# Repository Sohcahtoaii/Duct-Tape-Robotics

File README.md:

Robot pour la RoboCup – Catégorie Rescue Line Junior

Les fichiers de conception mécanique (CAO) ainsi que ceux de la carte électronique sont disponibles dans ce dépôt.

Une liste complète des pièces utilisées, avec des liens vers les composants, est également fournie.
Cependant, il est fortement recommandé de vérifier les empreintes (footprints) et les dimensions avant tout achat, afin d’éviter les erreurs de compatibilité.

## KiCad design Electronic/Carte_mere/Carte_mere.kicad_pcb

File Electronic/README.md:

Carte électronique du robot, liste des composants et librairy avec les componsants utilisés

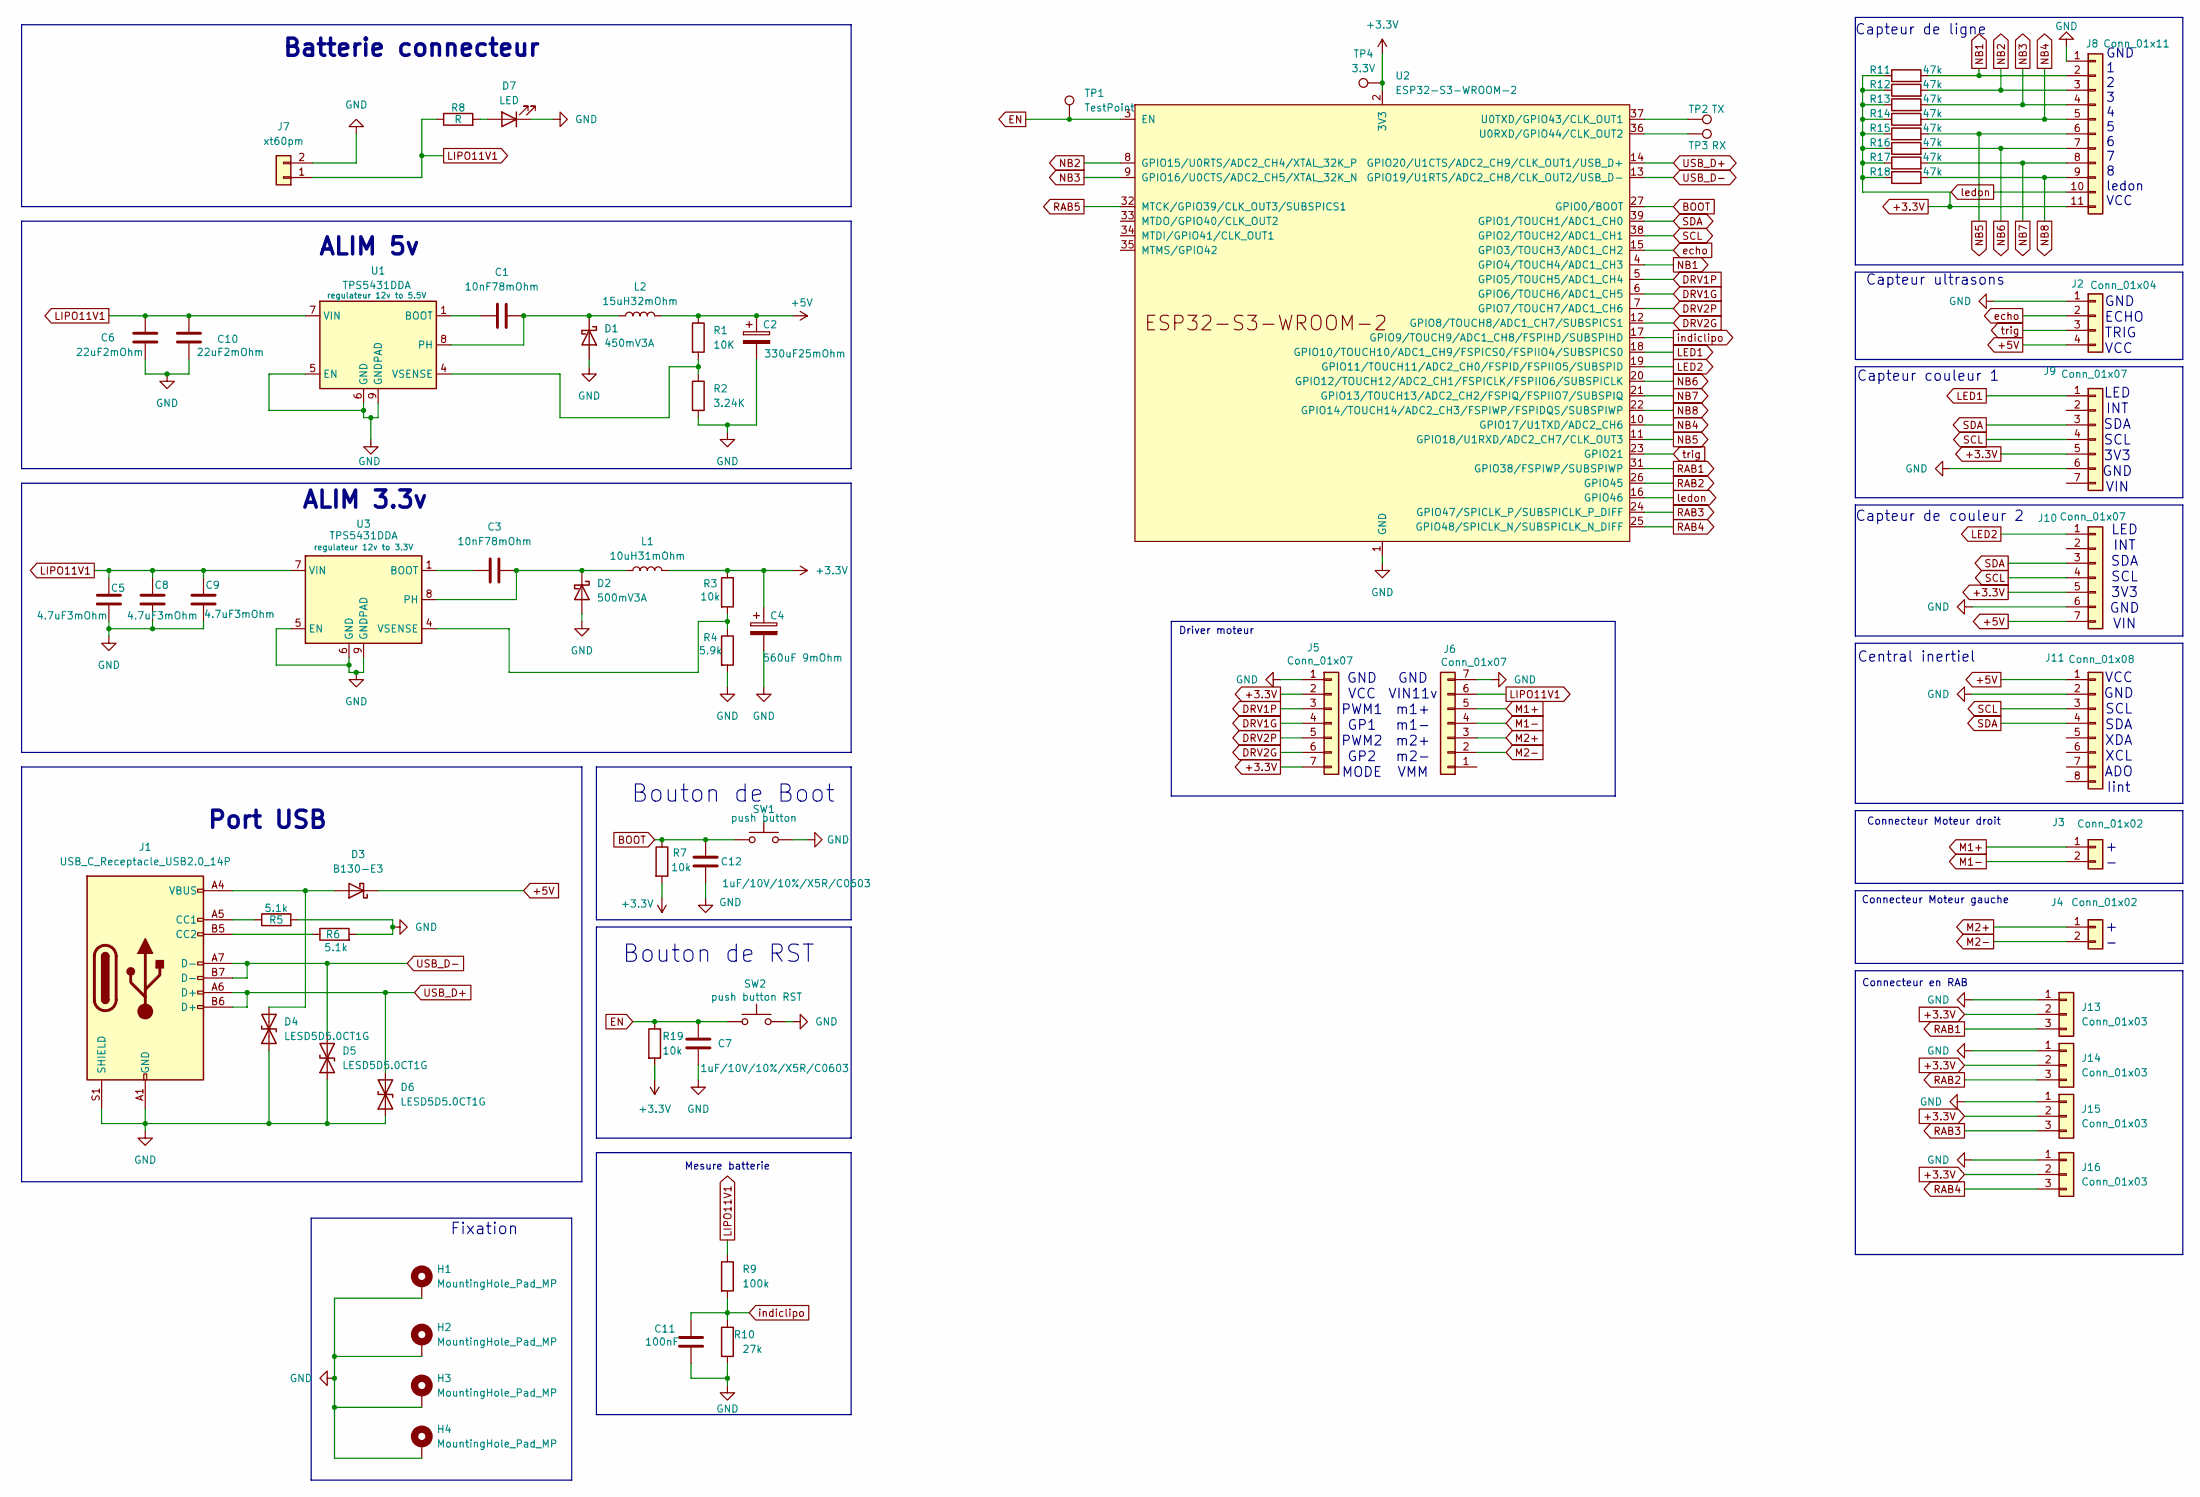
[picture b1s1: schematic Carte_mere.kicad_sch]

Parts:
C1, C3: 10nF78mOhm; C_0805_2012Metric_Pad1.18x1.45mm_HandSolder
C2: 330uF25mOhm; CP_Elec_10x12.6
C4: 560uF 9mOhm; CP_Elec_8x10.5
C5, C8, C9: 4.7uF3mOhm; C_0805_2012Metric_Pad1.18x1.45mm_HandSolder
C6, C10: 22uF2mOhm; C_0805_2012Metric_Pad1.18x1.45mm_HandSolder
C7, C12: 1uF/10V/10%/X5R/C0603; C_0805_2012Metric_Pad1.18x1.45mm_HandSolder
C11: 100nF; C_0805_2012Metric_Pad1.18x1.45mm_HandSolder
D1: 450mV3A; B340LA
D2: 500mV3A; B340LA
D3: B130-E3; D_SMA
D4, D5, D6: LESD5D5.0CT1G; LESD5D50CT1G
D7: LED; LED_0805_2012Metric_Pad1.15x1.40mm_HandSolder
H1, H2, H3, H4: MountingHole_Pad_MP; MountingHole_3.2mm_M3_DIN965_Pad_TopBottom
J1: USB_C_Receptacle_USB2.0_14P; USB_C_Receptacle_GCT_USB4105-xx-A_16P_TopMnt_Horizontal
J2: Conn_01x04; Molex_PicoBlade_53398-0471_1x04-1MP_P1.25mm_Vertical
J3, J4: Conn_01x02; 2843922
J5: Conn_01x07; PinSocket_1x07_P2.54mm_Vertical_SMD_Pin1Right
J6: Conn_01x07; PinSocket_1x07_P2.54mm_Vertical_SMD_Pin1Left
J7: xt60pm; XT60PWM
J8: Conn_01x11; Molex_PicoBlade_53261-1171_1x11-1MP_P1.25mm_Horizontal
J9, J10: Conn_01x07; Molex_PicoBlade_53261-0771_1x07-1MP_P1.25mm_Horizontal
J11: Conn_01x08; PinSocket_1x08_P2.54mm_Vertical_SMD_Pin1Right
J13, J14, J15, J16: Conn_01x03; PinHeader_1x03_P2.54mm_Vertical
L1: 10uH31mOhm; INDPM102100X510N
L2: 15uH32mOhm; INDPM120120X620N
R1: 10K; R_0805_2012Metric_Pad1.20x1.40mm_HandSolder
R2: 3.24K; R_0805_2012Metric_Pad1.20x1.40mm_HandSolder
R3, R7, R19: 10k; R_0805_2012Metric_Pad1.20x1.40mm_HandSolder
R4: 5.9k; R_0805_2012Metric_Pad1.20x1.40mm_HandSolder
R5, R6: 5.1k; R_0805_2012Metric_Pad1.20x1.40mm_HandSolder
R8: R; R_0805_2012Metric_Pad1.20x1.40mm_HandSolder
R9: 100k; R_0805_2012Metric_Pad1.20x1.40mm_HandSolder
R10: 27k; R_0805_2012Metric_Pad1.20x1.40mm_HandSolder
R11, R12, R13, R14, R15, R16, R17, R18: 47k; R_0805_2012Metric_Pad1.20x1.40mm_HandSolder
SW1: push button; SW_PUSH_6mm_H5mm
SW2: push button RST; SW_PUSH_6mm_H5mm
TP1: TestPoint; TestPoint_Pad_D1.5mm
TP2: TX; TestPoint_Pad_D1.5mm
TP3: RX; TestPoint_Pad_D1.5mm
TP4: 3.3V; TestPoint_Pad_D1.5mm
U1, U3: TPS5431DDA; TI_SO-PowerPAD-8_ThermalVias
U2: ESP32-S3-WROOM-2

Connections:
+3.3V: C4.1, J5.2, J5.7, J8.11, J9.5, J10.5, J13.2, J14.2, J15.2, J16.2, L1.2, R3.1, R7.2, R11.1, R12.1, R13.1, R14.1, R15.1, R16.1, R17.1, R18.1, R19.2, TP4.1, U2.2 (3V3)
+5V: C2.1, D3.1 (K), J2.4, J10.7, J11.1, L2.2, R1.1
BOOT: C12.1, R7.1, SW1.1, U2.27 (GPIO0/BOOT)
DRV1G: J5.4, U2.6 (GPIO6/TOUCH6/ADC1_CH5)
DRV1P: J5.3, U2.5 (GPIO5/TOUCH5/ADC1_CH4)
DRV2G: J5.6, U2.12 (GPIO8/TOUCH8/ADC1_CH7/SUBSPICS1)
DRV2P: J5.5, U2.7 (GPIO7/TOUCH7/ADC1_CH6)
EN: C7.1, R19.1, SW2.1, TP1.1, U2.3 (EN)
GND: C2.2, C4.2, C5.1, C6.1, C7.2, C8.1, C9.1, C10.1, C11.1, C12.2, D1.2 (A), D2.2 (A), D4.1 (A1), D5.1 (A1), D6.1 (A1), D7.1 (K), H1.MP, H2.MP, H3.MP, H4.MP, J1.A1 (GND), J1.A12 (GND), J1.B1 (GND), J1.B12 (GND), J1.S1 (SHIELD), J2.1, J5.1, J6.7, J7.2, J8.1, J9.6, J10.6, J11.2, J13.1, J14.1, J15.1, J16.1, R2.2, R4.2, R5.2, R6.2, R10.2, SW1.2, SW2.2, U1.5 (EN), U1.6 (GND), U1.9 (GNDPAD), U2.1 (GND), U2.40 (GND), U2.41 (GND), U3.5 (EN), U3.6 (GND), U3.9 (GNDPAD)
LED1: J9.1, U2.18 (GPIO10/TOUCH10/ADC1_CH9/FSPICS0/FSPIIO4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)
LED2: J10.1, U2.19 (GPIO11/TOUCH11/ADC2_CH0/FSPID/FSPIIO5/S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)
LIPO11V1: C5.2, C6.2, C8.2, C9.2, C10.2, J6.6, J7.1, R8.1, R9.1, U1.7 (VIN), U3.7 (VIN)
M1+: J3.1, J6.5
M1-: J3.2, J6.4
M2+: J4.1, J6.3
M2-: J4.2, J6.2
NB1: J8.2, R11.2, U2.4 (GPIO4/TOUCH4/ADC1_CH3)
NB2: J8.3, R12.2, U2.8 (GPIO15/U0RTS/ADC2_CH4/XTAL_32K_P)
NB3: J8.4, R13.2, U2.9 (GPIO16/U0CTS/ADC2_CH5/XTAL_32K_N)
NB4: J8.5, R14.2, U2.10 (GPIO17/U1TXD/ADC2_CH6)
NB5: J8.6, R15.2, U2.11 (GPIO18/U1RXD/ADC2_CH7/CLK_OUT3)
NB6: J8.7, R16.2, U2.20 (GPIO12/TOUCH12/ADC2_CH1/FSPICLK/FSPIIO6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)
NB7: J8.8, R17.2, U2.21 (GPIO13/TOUCH13/ADC2_CH2/FSPIQ/FSPIIO7/S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)
NB8: J8.9, R18.2, U2.22 (GPIO14/TOUCH14/ADC2_CH3/FSPIWP/FSPIDQS/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)
unnamed: C1.2, D1.1 (K), L2.1, U1.8 (PH)
unnamed: C3.2, D2.1 (K), L1.1, U3.8 (PH)
unnamed: D3.2 (A), D4.2 (A2), J1.A4 (VBUS), J1.A9 (VBUS), J1.B4 (VBUS), J1.B9 (VBUS)
unnamed: D7.2 (A), R8.2
unnamed: J1.A5 (CC1), R5.1
unnamed: J1.B5 (CC2), R6.1
unnamed: C1.1, U1.1 (BOOT)
unnamed: R1.2, R2.1, U1.4 (VSENSE)
unnamed: TP3.1, U2.36 (U0RXD/GPIO44/CLK_OUT2)
unnamed: TP2.1, U2.37 (U0TXD/GPIO43/CLK_OUT1)
unnamed: C3.1, U3.1 (BOOT)
unnamed: R3.2, R4.1, U3.4 (VSENSE)
RAB1: J13.3, U2.31 (GPIO38/FSPIWP/SUBSPIWP)
RAB2: J14.3, U2.26 (GPIO45)
RAB3: J15.3, U2.24 (GPIO47/SPICLK_P/SUBSPICLK_P_DIFF)
RAB4: J16.3, U2.25 (GPIO48/SPICLK_N/SUBSPICLK_N_DIFF)
RAB5: U2.32 (MTCK/GPIO39/CLK_OUT3/SUBSPICS1)
SCL: J9.4, J10.4, J11.3, U2.38 (GPIO2/TOUCH2/ADC1_CH1)
SDA: J9.3, J10.3, J11.4, U2.39 (GPIO1/TOUCH1/ADC1_CH0)
USB_D+: D6.2 (A2), J1.A6 (D+), J1.B6 (D+), U2.14 (GPIO20/U1CTS/ADC2_CH9/CLK_OUT1/USB_D+)
USB_D-: D5.2 (A2), J1.A7 (D-), J1.B7 (D-), U2.13 (GPIO19/U1RTS/ADC2_CH8/CLK_OUT2/USB_D-)
echo: J2.2, U2.15 (GPIO3/TOUCH3/ADC1_CH2)
indiclipo: C11.2, R9.2, R10.1, U2.17 (GPIO9/TOUCH9/ADC1_CH8/FSPIHD/SUBSPIHD)
ledon: J8.10, U2.16 (GPIO46)
trig: J2.3, U2.23 (GPIO21)

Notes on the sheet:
GND ECHO TRIG VCC
Batterie connecteur
Capteur couleur 1
Driver moteur
ALIM 3.3v
Bouton de Boot
+ -
LED INT SDA SCL 3V3 GND VIN
Connecteur Moteur droit
Connecteur Moteur gauche
GND 1 2 3 4 5 6 7 8 ledon VCC
Capteur de couleur 2
Fixation
Capteur de ligne
Capteur ultrasons
Mesure batterie
VCC GND SCL SDA XDA XCL ADO Iint
GND VCC PWM1 GP1 PWM2 GP2 MODE
Central inertiel
Bouton de RST
Connecteur en RAB
GND VIN11v m1+ m1- m2+ m2- VMM
ALIM 5v
Port USB

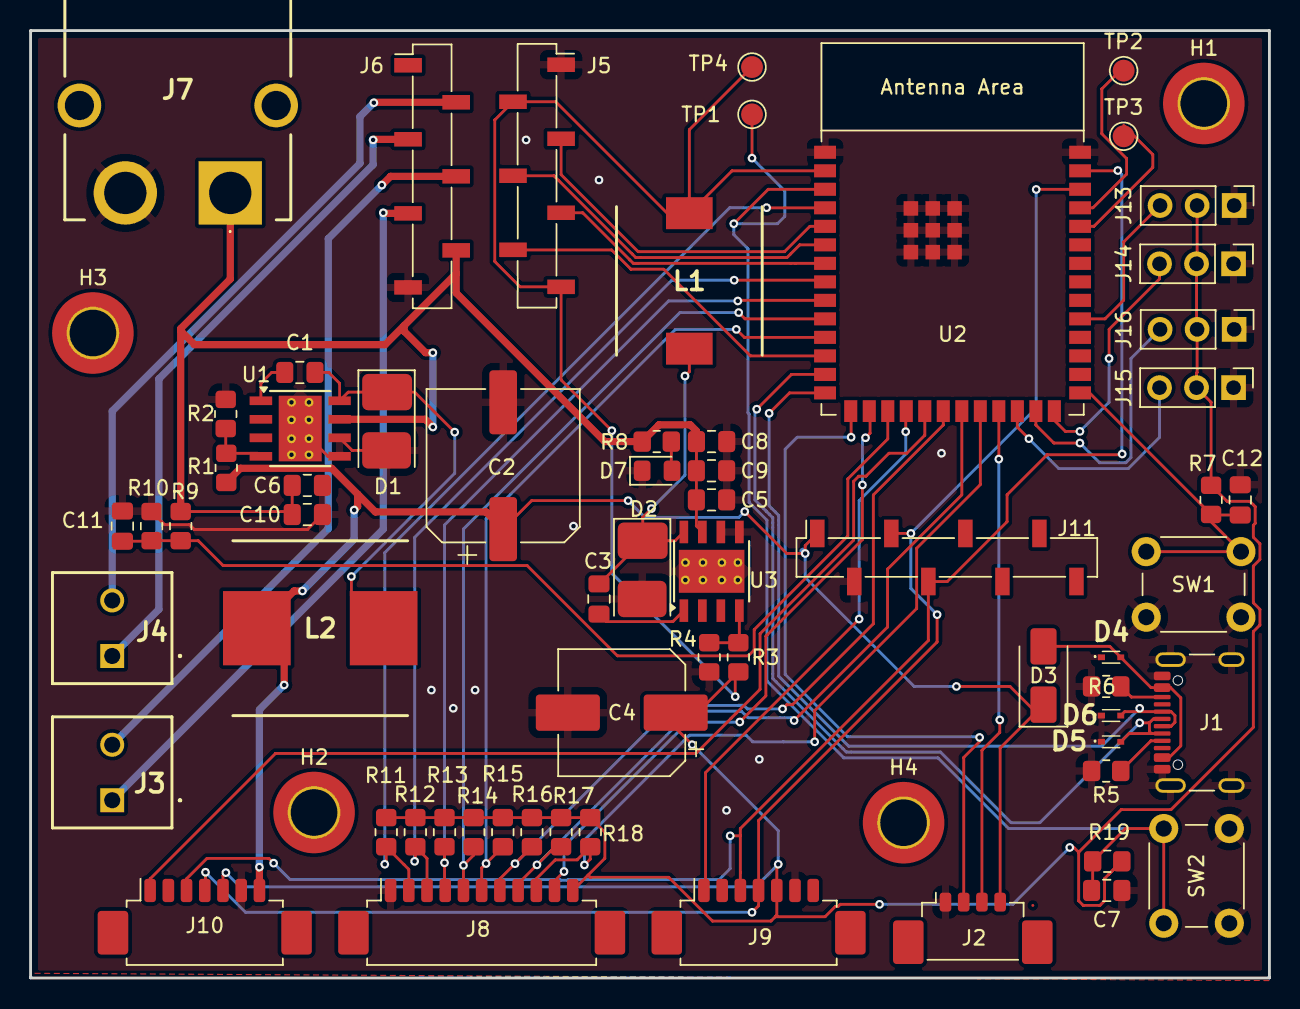
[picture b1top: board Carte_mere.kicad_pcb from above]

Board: 2 copper layers, 85.0 x 65.0 mm, 68 parts (0 on the bottom side), 48 nets.

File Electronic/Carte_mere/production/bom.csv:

Designator,Footprint,Quantity,Value,LCSC Part #
"C1, C3",0805,2,10nF78mOhm,
"C10, C6",0805,2,22uF2mOhm,
C11,0805,1,100nF,
"C12, C7",0805,2,1uF/10V/10%/X5R/C0603,
C2,CP_Elec_10x12.6,1,330uF25mOhm,
C4,CP_Elec_8x10.5,1,560uF 9mOhm,
"C5, C8, C9",0805,3,4.7uF3mOhm,
D1,B340LA,1,450mV3A,
D2,B340LA,1,500mV3A,
D3,D_SMA,1,B130-E3,
"D4, D5, D6",LESD5D50CT1G,3,LESD5D5.0CT1G,
D7,0805,1,LED,
J1,USB_C_Receptacle_GCT_USB4105-xx-A_16P_TopMnt_Horizontal,1,USB_C_Receptacle_USB2.0_14P,
"J10, J9",Molex_PicoBlade_53261-0771_1x07-1MP_P1.25mm_Horizontal,2,Conn_01x07,
J11,PinSocket_1x08_P2.54mm_Vertical_SMD_Pin1Right,1,Conn_01x08,
J2,Molex_PicoBlade_53398-0471_1x04-1MP_P1.25mm_Vertical,1,Conn_01x04,
"J3, J4",2843922,2,Conn_01x02,
J5,PinSocket_1x07_P2.54mm_Vertical_SMD_Pin1Right,1,Conn_01x07,
J6,PinSocket_1x07_P2.54mm_Vertical_SMD_Pin1Left,1,Conn_01x07,
J7,XT60PWM,1,xt60pm,
J8,Molex_PicoBlade_53261-1171_1x11-1MP_P1.25mm_Horizontal,1,Conn_01x11,
L1,INDPM102100X510N,1,10uH31mOhm,
L2,INDPM120120X620N,1,15uH32mOhm,
"R1, R19, R3, R7",0805,4,10K,
R10,0805,1,27k,
"R11, R12, R13, R14, R15, R16, R17, R18",0805,8,47k,
R2,0805,1,3.24K,
R4,0805,1,5.9k,
"R5, R6",0805,2,5.1k,
R8,0805,1,R,
R9,0805,1,100k,
SW1,SW_PUSH_6mm_H5mm,1,push button,
SW2,SW_PUSH_6mm_H5mm,1,push button RST,
"U1, U3",TI_SO-PowerPAD-8_ThermalVias,2,TPS5431DDA,
U2,ESP32-S3-WROOM-2,1,ESP32-S3-WROOM-2,

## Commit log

2025-03-17 Create README.md
    add file to make category
2025-04-09 Delete Electronic/Carte_mere directory
    delete before reupload
2025-04-09 final peut êtres
2025-05-19 Add MotorLib
2025-05-20 Rename piece robot.ods to BOM(liste de pieces.ods
2025-05-20 Rename BOM(liste de pieces.ods to BOM(liste de pieces).ods
